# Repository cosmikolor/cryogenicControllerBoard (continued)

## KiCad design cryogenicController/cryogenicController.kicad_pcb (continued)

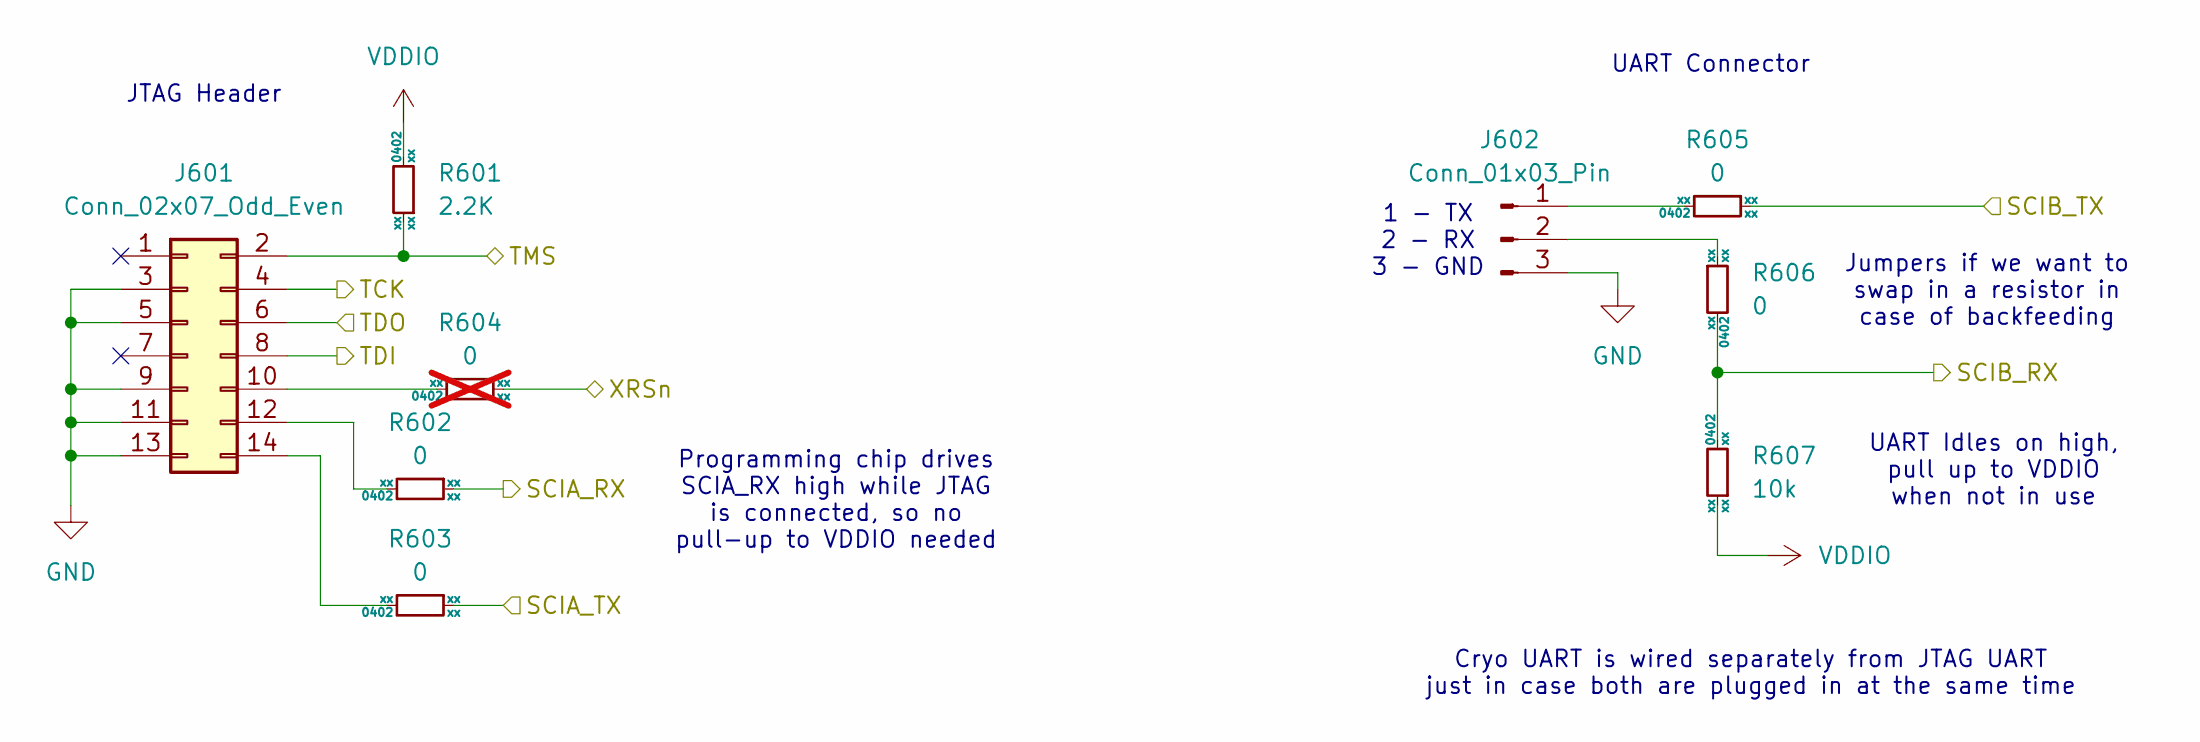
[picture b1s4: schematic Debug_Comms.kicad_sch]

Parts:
J601: Conn_02x07_Odd_Even; SAMTEC_FTSH-107-01-X-DV-K; MfrPN FTSH-107-01-F-DV-K
J602: Conn_01x03_Pin; PinHeader_1x03_P2.54mm_Vertical
R601: 2.2K; R_0402_1005Metric; Tolerance xx; Voltage xx
R602, R603, R605, R606: 0; R_0402_1005Metric; Tolerance xx; Voltage xx
R604: 0; R_0402_1005Metric; Tolerance xx; Voltage xx; not fitted
R607: 10k; R_0402_1005Metric; Tolerance xx; Voltage xx

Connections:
/JTAG_UART/SCIA_RX: R602.1; also elsewhere on the board
/JTAG_UART/SCIA_TX: R603.1; also elsewhere on the board
/JTAG_UART/SCIB_RX: R606.2, R607.2; also elsewhere on the board
/JTAG_UART/SCIB_TX: R605.1; also elsewhere on the board
/JTAG_UART/TCK: J601.4; also elsewhere on the board
/JTAG_UART/TDI: J601.8; also elsewhere on the board
/JTAG_UART/TDO: J601.6; also elsewhere on the board
/JTAG_UART/TMS: J601.2, R601.1; also elsewhere on the board
/JTAG_UART/XRSn: R604.1; also elsewhere on the board
GND: J601.3, J601.5, J601.9, J601.11, J601.13, J602.3; also elsewhere on the board
unnamed: J601.10, R604.2
unnamed: J601.12, R602.2
unnamed: J601.14, R603.2
unnamed: J602.1, R605.2
unnamed: J602.2, R606.1
VDDIO: R601.2, R607.1; also elsewhere on the board

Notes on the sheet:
1 - TX 2 - RX 3 - GND
UART Connector
Cryo UART is wired separately from JTAG UART just in case both are plugged in at the same time
JTAG Header
Jumpers if we want to swap in a resistor in case of backfeeding
UART Idles on high, pull up to VDDIO when not in use
Programming chip drives SCIA_RX high while JTAG is connected, so no pull-up to VDDIO needed

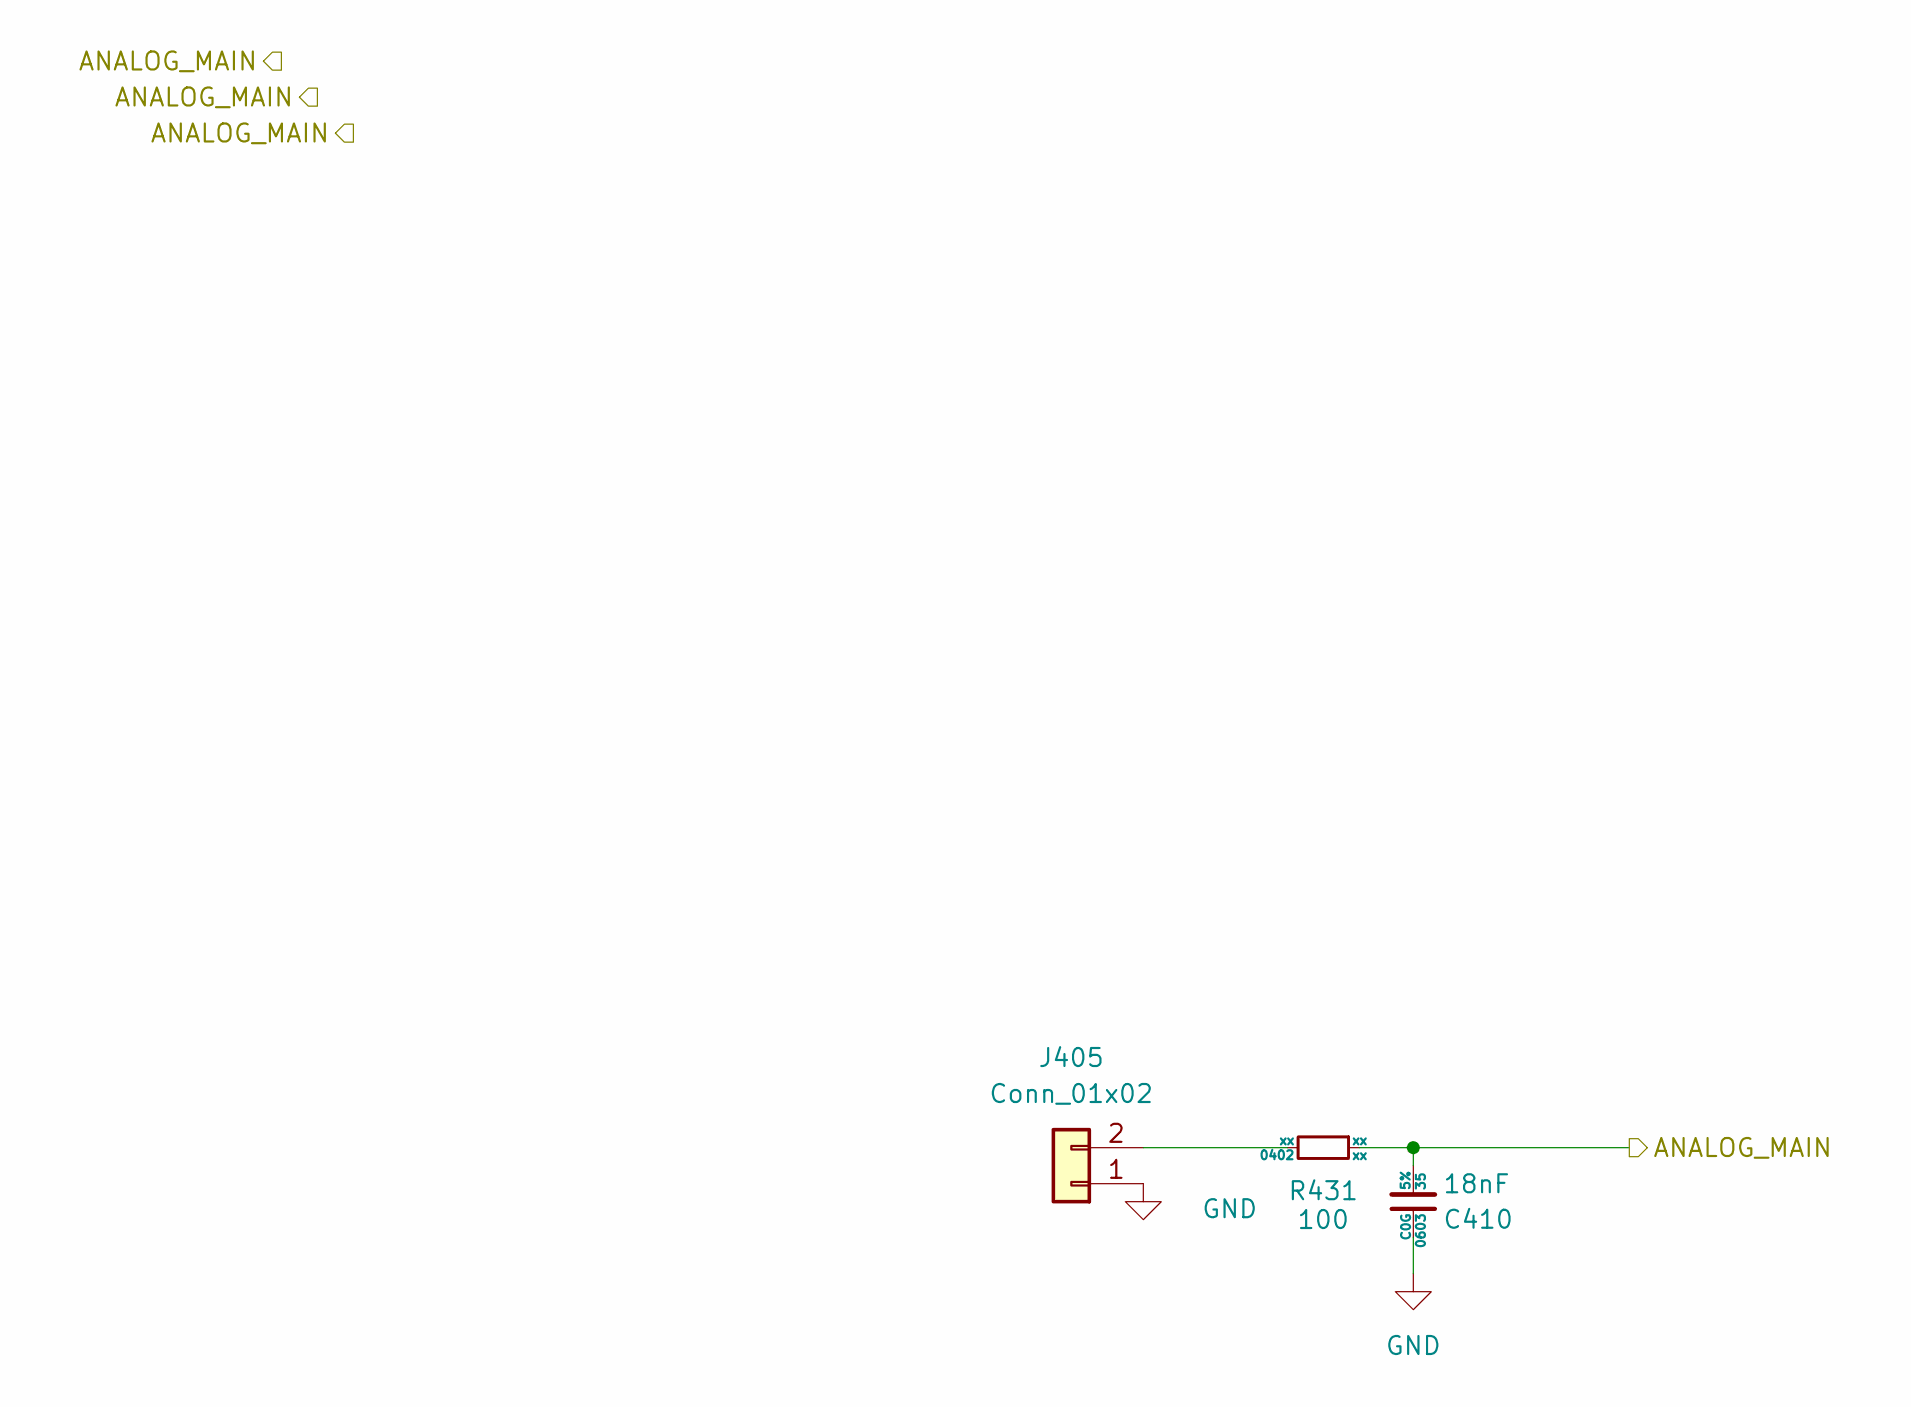
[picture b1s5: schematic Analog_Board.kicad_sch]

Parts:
C410: 18nF; C_0603_1608Metric; Voltage 35; Tolerance 5%
J405: Conn_01x02; PinHeader_1x02_P2.54mm_Vertical
R431: 100; R_0402_1005Metric; Tolerance xx; Voltage xx

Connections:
/Analog_Board/ANALOG_MAIN: C410.2, R431.1; also elsewhere on the board
GND: C410.1, J405.1; also elsewhere on the board
unnamed: J405.2, R431.2

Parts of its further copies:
C411, C412: 18nF; C_0603_1608Metric; Voltage 35; Tolerance 5%
J406, J407: Conn_01x02; PinHeader_1x02_P2.54mm_Vertical
R432, R433: 100; R_0402_1005Metric; Tolerance xx; Voltage xx

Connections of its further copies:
/Analog_Board1/ANALOG_MAIN: C411.2, R432.1; also elsewhere on the board
/Analog_Board2/ANALOG_MAIN: C412.2, R433.1; also elsewhere on the board
GND: C411.1, C412.1, J406.1, J407.1; also elsewhere on the board
unnamed: J406.2, R432.2
unnamed: J407.2, R433.2

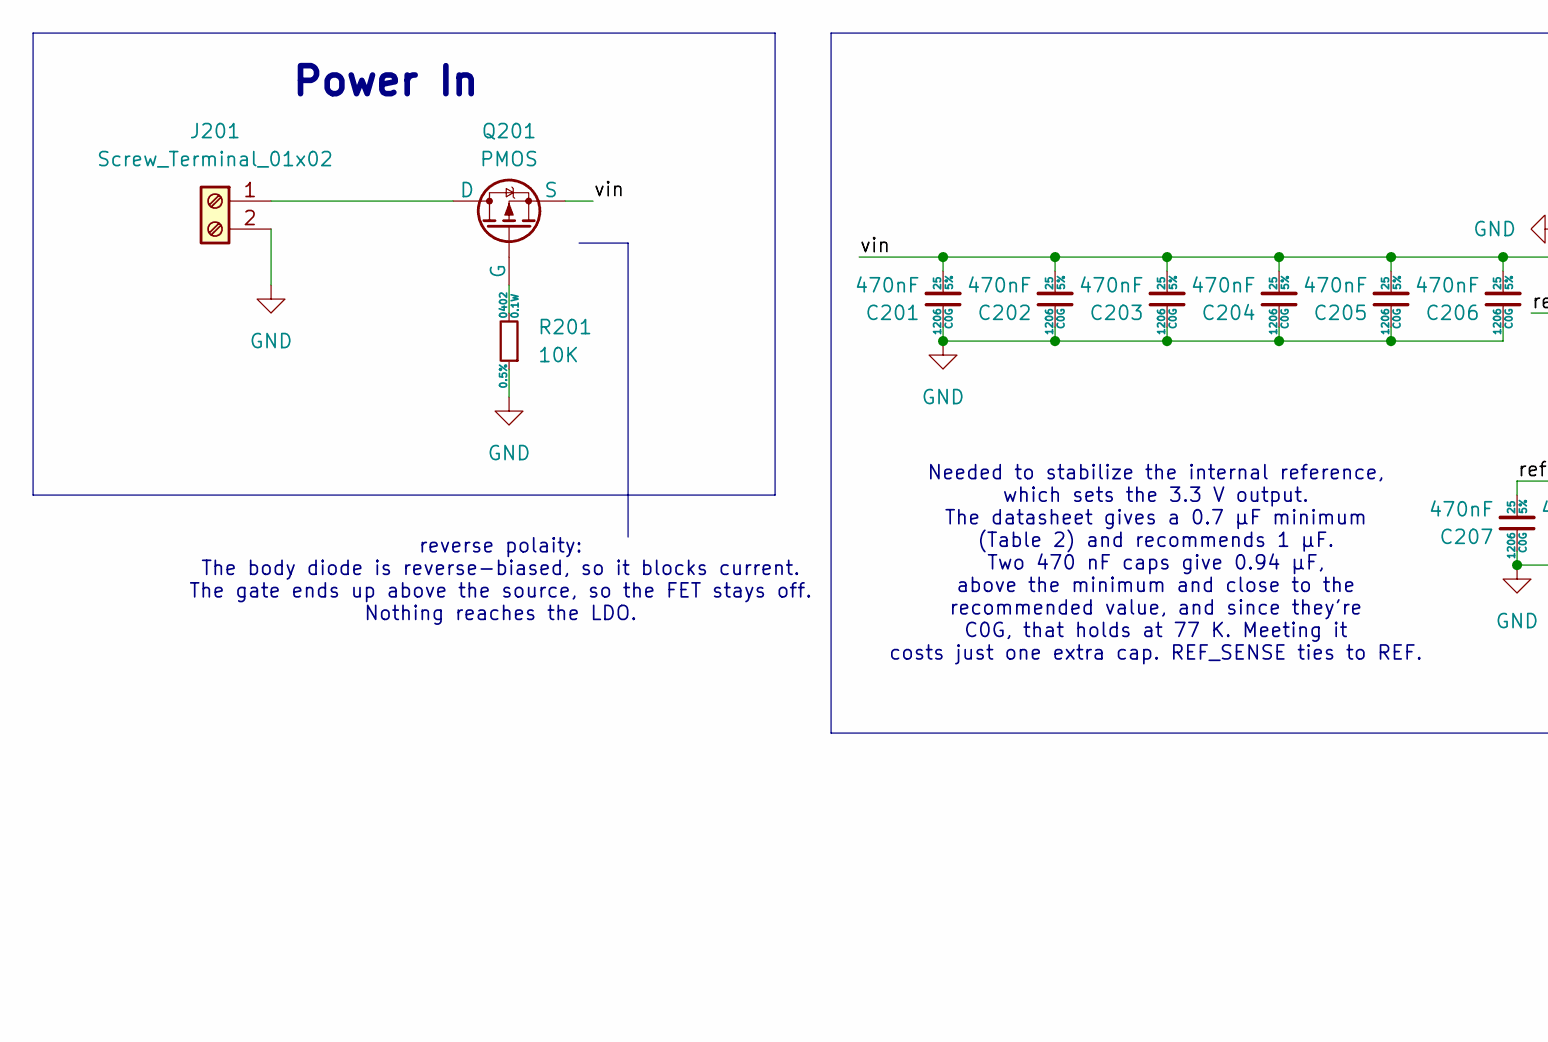
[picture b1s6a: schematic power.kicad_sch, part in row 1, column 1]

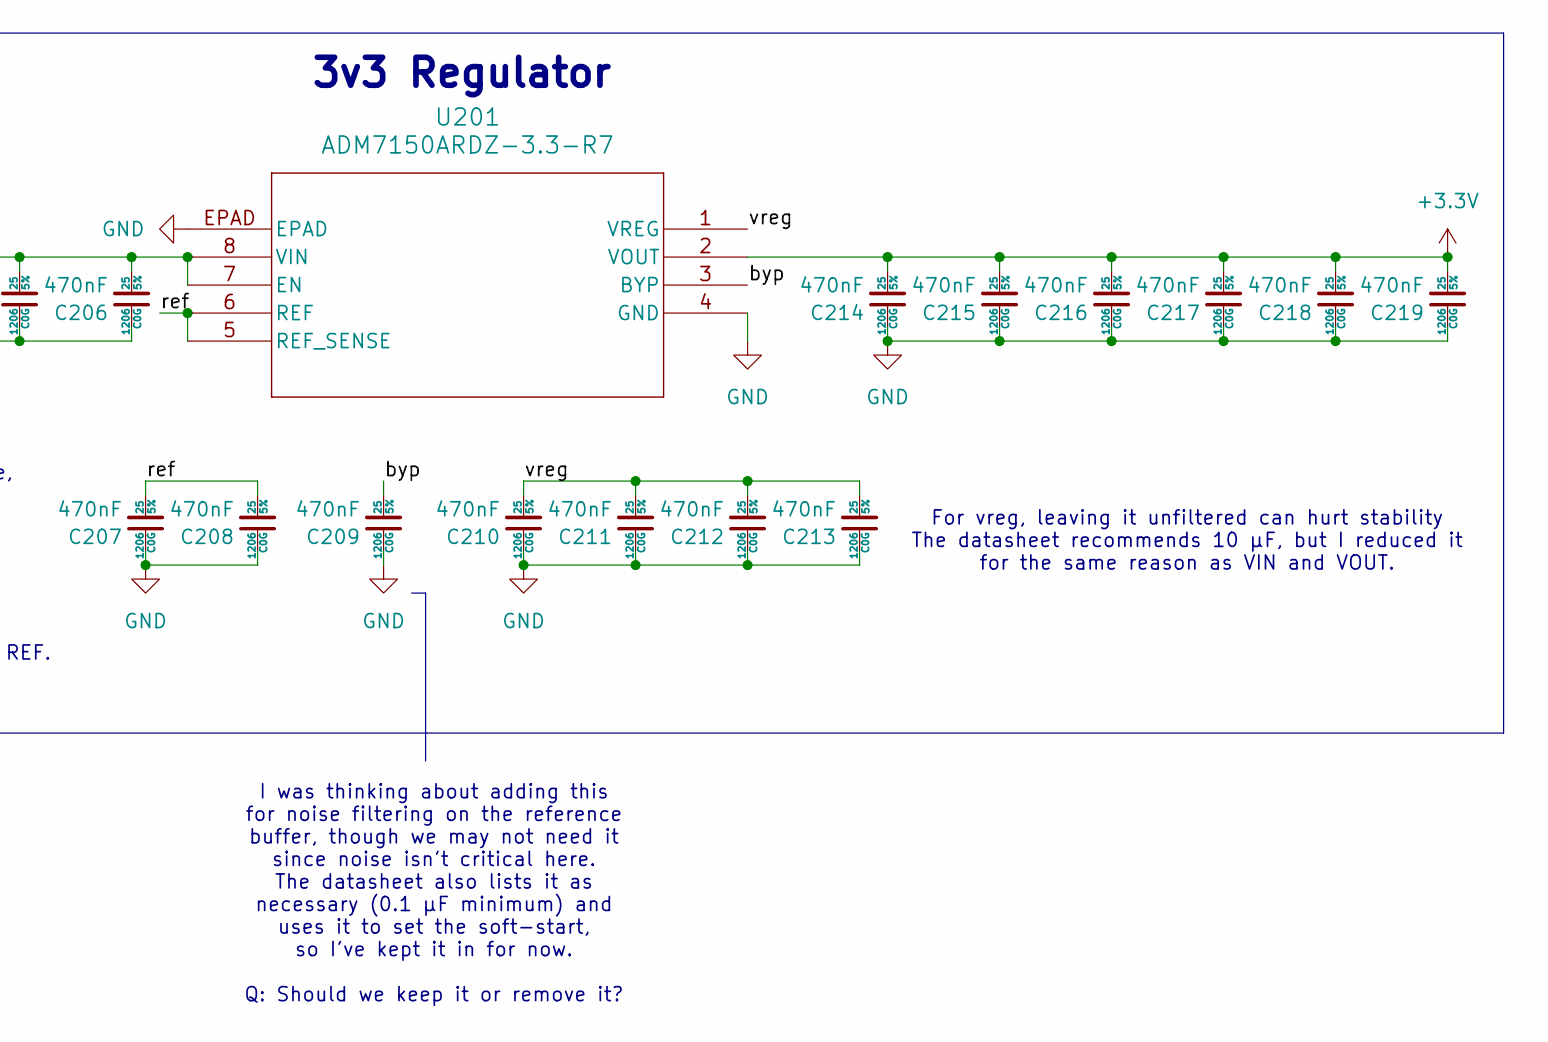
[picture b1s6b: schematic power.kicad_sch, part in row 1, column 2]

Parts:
C201, C202, C203, C204, C205, C206, C207, C208, C209, C210, C211, C212, C213, C214, C215, C216, C217, C218, C219: 470nF; C_1206_3216Metric; Voltage 25; Tolerance 5%; MfrPN GRM31C5C1E474JE01L
J201: Screw_Terminal_01x02; TerminalBlock_Phoenix_MKDS-1,5-2-5.08_1x02_P5.08mm_Horizont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
Q201: PMOS; SOT-23
R201: 10K; R_0402_1005Metric; Tolerance 0.5%
U201: ADM7150ARDZ-3.3-R7; SOIC-8-1EP_3.9x4.9mm_P1.27mm_EP2.41x3.3mm

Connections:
+3.3V: C214.2, C215.2, C216.2, C217.2, C218.2, C219.2, U201.2 (VOUT); also elsewhere on the board
/power/byp: C209.2, U201.3 (BYP)
/power/ref: C207.2, C208.2, U201.5 (REF_SENSE), U201.6 (REF)
/power/vin: C201.2, C202.2, C203.2, C204.2, C205.2, C206.2, Q201.3 (S), U201.7 (EN), U201.8 (VIN)
/power/vreg: C210.2, C211.2, C212.2, C213.2, U201.1 (VREG)
GND: C201.1, C202.1, C203.1, C204.1, C205.1, C206.1, C207.1, C208.1, C209.1, C210.1, C211.1, C212.1, C213.1, C214.1, C215.1, C216.1, C217.1, C218.1, C219.1, J201.2, R201.1, U201.4 (GND), U201.EPAD; also elsewhere on the board
unnamed: J201.1, Q201.1 (D)
unnamed: Q201.2 (G), R201.2

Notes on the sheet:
reverse polaity: The body diode is reverse-biased, so it blocks current. The gate ends up above the source, so the FET stays off. Nothing reaches the LDO.
Needed to stabilize the internal reference, which sets the 3.3 V output. The datasheet gives a 0.7 µF minimum (Table 2) and recommends 1 µF. Two 470 nF caps give 0.94 µF, above the minimum and close to the recommended value, and since they're C0G, that holds at 77 K. Meeting it costs just one extra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
Power In
For vreg, leaving it unfiltered can hurt stability The datasheet recommends 10 µF, but I reduced it for the same reason as VIN and VOUT.
I was thinking about adding this for noise filtering on the reference buffer, though we may not need it since noise isn't critical here. The datasheet also lists it as necessary (0.1 µF minimum) and uses it to set the soft-start, so I've kept it in for now. Q: Should we keep it or remove it?
3v3 Regulator

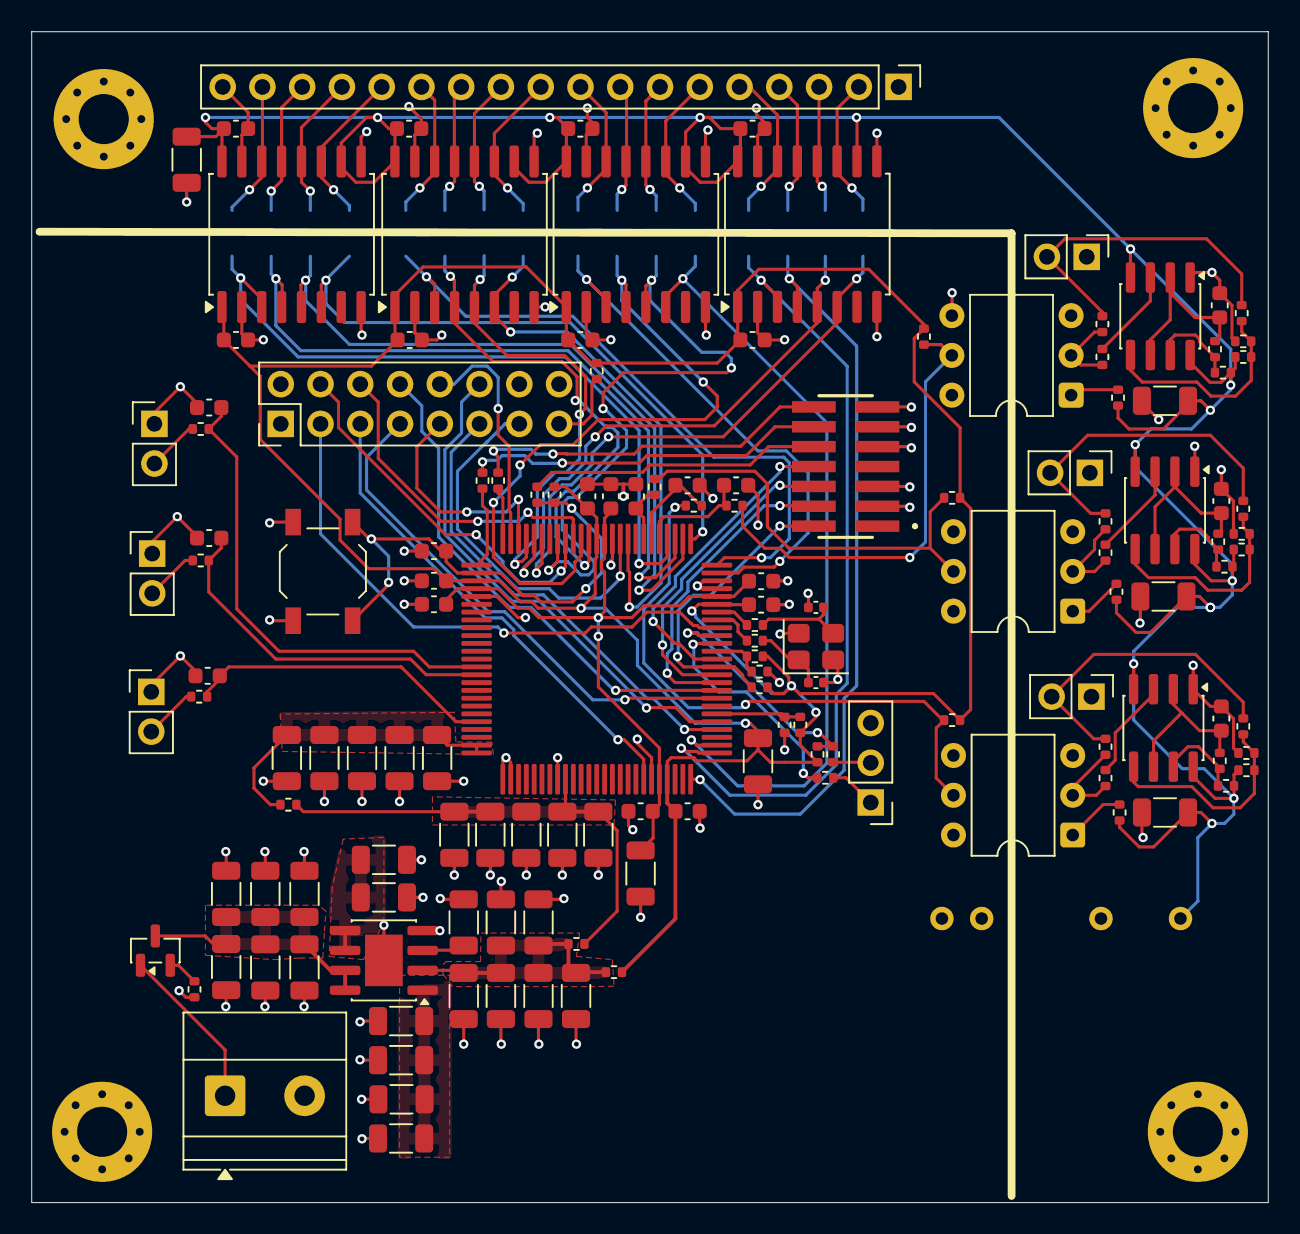
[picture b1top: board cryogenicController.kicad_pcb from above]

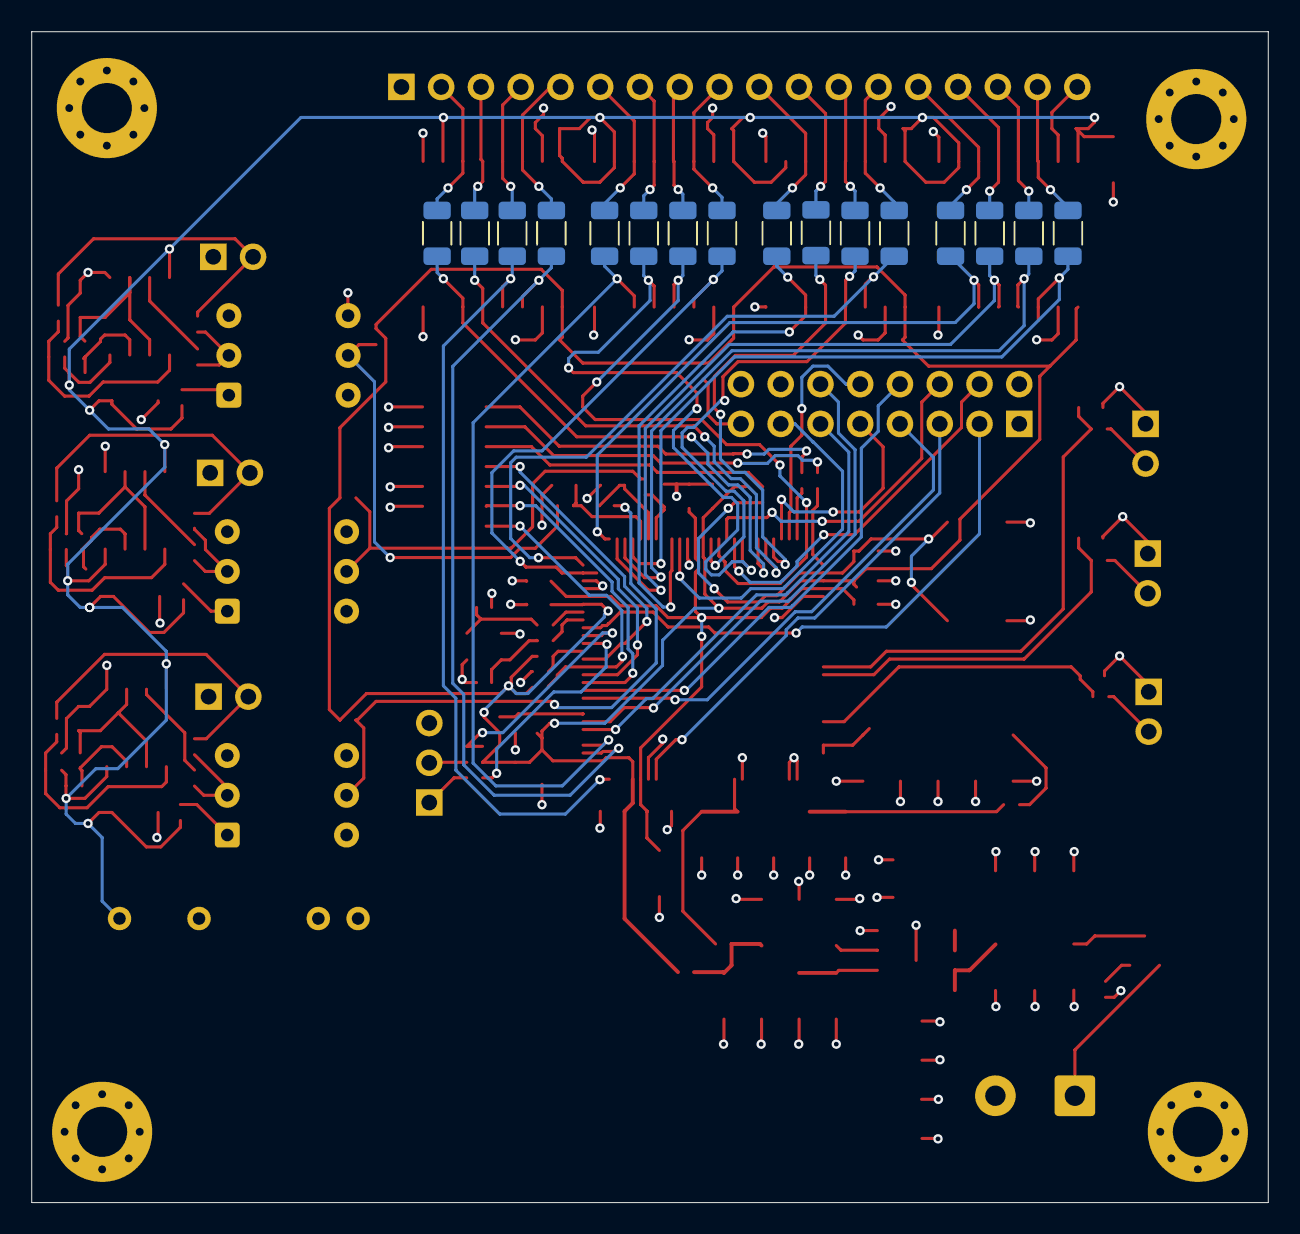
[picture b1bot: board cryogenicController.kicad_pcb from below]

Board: 4 copper layers, 79.0 x 74.8 mm, 158 parts (16 on the bottom side), 111 nets.
